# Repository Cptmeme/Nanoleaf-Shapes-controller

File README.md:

# Nanoleaf Shapes controller

An open-source replacement controller for **Nanoleaf Shapes** panels. A small interface board plugs into a
single panel edge and takes **42 V, GND and DATA** from it: no stock controller and no separate power supply.

<p align="center">
  
</p>
<p align="center"><em>An early board (foreground) driving nine Mini Triangles through a cut flex linker. Click for the video.</em></p>

It runs one of four firmwares:

- **WLED**, through a drop-in [usermod](wled/usermod/nanoleaf_shapes/) that needs no changes to WLED itself
  (recommended), or the original [core patch](wled/core-patch/). You get effects, 2D effects laid out on the
  real panel shape, the WLED apps and Home Assistant. See [`wled/`](wled/).
- **A standalone ESP-IDF firmware** with a Wi-Fi console, status page, OTA updates and a DDP receiver. It's
  useful for bring-up, protocol work, or as a network target for another WLED instance. See [`firmware/`](firmware/).
- **Matter over Thread**, built on [esp-matter](https://github.com/espressif/esp-matter): the panels become
  one Matter colour light for Apple Home, Google Home or Home Assistant, plus a switch that runs a moving
  rainbow. It talks Thread instead of Wi-Fi and pairs over Bluetooth. See [`matter-over-thread/`](matter-over-thread/).
- **[LeafBus](https://github.com/MyrikLD/LeafBus)**, MyrikLD's original MicroPython firmware, whose protocol work
  this project builds on. The panels become a DDP and E1.31/sACN pixel sink with a layout page. It needs three
  settings on this board, and hasn't been tested on it yet; see [Running LeafBus](#running-leafbus).

> **Status:** the hardware is built and working with an ESP32-C5 module, driving 9 Mini Triangles in chain,
> fork and ring layouts, with WLED (the core-patch build), with the ESP-IDF firmware, and as a Matter light in
> a Thread network.
> Hexagons and large Triangles are handled by the code but have not been tested on real panels yet.
> **Rev B is built and working**, with USB-C flashing, three buttons on the case and a printed
> enclosure. The project files in this repository are now **rev C**, which is rev B with the faults its
> bring-up exposed. No rev C board has been fabricated. See [Current board](#current-board-rev-c).

## Repository

| Path | Contents |
|---|---|
| [`hardware/`](hardware/) | Rev C KiCad project (schematic and PCB), fabrication files in `fab/`, and the printable case STLs in `mechanical/`. Rev B is built and working, rev C is rev B with its bring-up fixes and has not been fabricated |
| [`firmware/`](firmware/) | ESP-IDF firmware |
| [`wled/`](wled/) | WLED integration: the usermod (recommended) and the original core patch, each with build instructions |
| [`matter-over-thread/`](matter-over-thread/) | Matter-over-Thread firmware (esp-matter) |
| [`docs/protocol-notes.md`](docs/protocol-notes.md) | Panel bus behaviour measured on real panels, since merged into the LeafBus spec and credited there |

## Hardware

**Power:** 42 V from `J1` goes to a TPS54360 buck converter (`U1`), which makes 3.31 V (`R2` 47k / `R3` 15k,
`R5` 330k for 295 kHz, `L1` 33 µH, `D1` SS210). That's plenty for an ESP32 with Wi-Fi.

**Panel bus:** this uses the same method as the stock controller: two 74LVC1G125 tri-state buffers.
- `U4` transmits. Its output is enabled only while TX is active, by a one-shot (`D2` 1N4148W, `R7` 10k,
  `C17` 220 pF, about 1.3 µs), so the line is released between bytes.
- `U3` always receives, so the controller hears its own echo (the firmware strips it).
- `R1` (2.2 kΩ) sits in series with the bus and `R6` (1 kΩ) with RX. `R10` (1 kΩ) lets a GPIO drive the
  one-shot node for optional RS485-style direction control.

**Module:** any 16 × 24 mm module with the ESP-12F footprint. The footprint is drawn for the Wireless-Tag
WT0132C6-S5 (ESP32-C6); the working boards use a DOIT ESPC5-12 (ESP32-C5). The module sits on the back, and
is hand-soldered along with `SW1` and `SW2`.

### Module pins

| Net | Module pin (WT0132C6-S5 numbering) | ESP32-C6 | ESP32-C5 (ESPC5-12, verified) |
|---|---|---|---|
| Bus TX | 20 | GPIO3 | GPIO26 |
| Bus RX | 19 | GPIO10 | GPIO27 |
| One-shot (RC) node | 16 | GPIO7 | GPIO6 |
| BOOT button `SW2` | 18 | GPIO9 | GPIO28 |
| UART0 RX / TX | 21 / 22 | GPIO17 / GPIO16 | GPIO12 / GPIO11 |

For other modules, the ESP-IDF firmware finds the bus pins itself (`pinscan`) by exercising the on-board
`U4` → `U3` loopback.

### Connectors

| Connector | Pin 1 | Pin 2 | Pin 3 |
|---|---|---|---|
| `J1`, to a panel | 42 V | GND | DATA |

`J1` is three bare pads, not a header: the board clips beside a panel on a standard rigid Nanoleaf linker
and the linker's spring contacts press on them. There is nothing to wire up, and nothing to get the wrong
way round.

### Power and safety

- **Powered from the panels through `J1`:** the normal mode, and on a rev B board the only one. Wi-Fi,
  Bluetooth and Thread all work reliably on it.
- **Powered from USB:** rev C adds `D5`, a second SS210 from USB VBUS to the buck input, so the board runs
  from a USB host with no panel attached. With a panel connected, that node sits at 42 V and the diode is
  reverse biased, so nothing can reach the host. Without one, the buck runs from about 4.75 V, which leaves
  only ~0.25 V over the TPS54360's minimum: fine for bench flashing at 100-300 mA, not guaranteed on a long
  thin cable. On rev B, USB is data only and flashing needs a panel attached for power.
- **`D3`, an SMAJ48A, clamps the 42 V rail.** The board gets clipped onto live panels routinely, and
  hot-plugging into ceramic input capacitors can ring well above 42 V.
- **There is no fuse and no reverse-polarity protection**, left out on purpose: the linker mates one way
  only and `J1` is three bare pads, so there is nothing to connect backwards.

## Firmware

| | WLED ([`wled/`](wled/)) | Matter ([`matter-over-thread/`](matter-over-thread/)) | ESP-IDF firmware ([`firmware/`](firmware/)) |
|---|---|---|---|
| Use | Everyday lighting: effects, apps, Home Assistant | Smart-home light: Apple Home, Google Home, Home Assistant | Bring-up, diagnostics, protocol exploration |
| Network | Wi-Fi | Thread (needs a Thread border router); pairing over Bluetooth | Wi-Fi |
| Panel colours | WLED effects, including 2D on the real layout | One colour for all panels, white temperature, brightness; a rainbow switch | Console commands, or DDP from any sender |
| Touch | Not yet wired to WLED actions | Not yet exposed | Logged; "touch light" demo |
| Updates | WLED's update page | Serial (keeps the pairing); Matter OTA is enabled but untested | HTTP OTA with rollback |
| Chips | Usermod: builds for C5 and C6, not yet run on hardware. Core patch: tested on C5, C6 untested, also compiles for C3 and S3 | C5 (tested) and C6 (builds, untested) | Tested on C5 |

All three drive the panels the same way: they enumerate the layout at start-up, poll the panels every 50 ms,
and re-enumerate when panels are added or removed while running.

### Running LeafBus

[LeafBus](https://github.com/MyrikLD/LeafBus) is written for an original ESP32 wired to the panel through a
resistor. To run it on this board, change three things (this hasn't been tested on the board yet):

1. **MicroPython v1.29 or later for your module:** [ESP32_GENERIC_C5](https://micropython.org/download/ESP32_GENERIC_C5/)
   for the ESPC5-12, or [ESP32_GENERIC_C6](https://micropython.org/download/ESP32_GENERIC_C6/) for the
   WT0132C6-S5. See [Flashing](#flashing) for download mode.
2. **This board's bus pins in `config.json`:** `"uart": {"tx": 26, "rx": 27}` on the ESP32-C5, or
   `{"tx": 3, "rx": 10}` on the ESP32-C6.
3. **`open_drain=False` where `app.py` creates the bus:**
   `panelbus.PanelBus(tx=cfg['uart']['tx'], rx=cfg['uart']['rx'], open_drain=False)`. This board doesn't need
   open drain, because its tri-state buffer releases the line after every byte. LeafBus's open-drain switch
   also writes a register that only exists on the original ESP32.

Then copy the files as in LeafBus's quick start.

## Flashing

**Flashing goes over USB-C.** `U5`, a CH340C, carries UART0 with auto-reset, so there is no separate
adapter to wire up and no buttons to hold.

- **Rev C:** the standard tooling works as it comes. `idf.py -p PORT flash`, or `esptool` with its own
  default reset.
- **Rev B:** the CH340C's handshake lines reach the two reset transistors the opposite way round from the
  circuit esptool assumes, so its reset asserts BOOT where it means to assert EN and the chip never enters
  the ROM loader. It fails as `Invalid head of packet` or `No serial data received`, which reads like a bad
  cable. Use `firmware/tools/revb_reset.py download`, flash with `--before no_reset`, then
  `firmware/tools/revb_reset.py run`. Rev B's USB is data only, so the board needs a panel attached for
  power, and 115200 is more reliable than 460800 on this link.

After the first flash, WLED and the ESP-IDF firmware update over Wi-Fi. The Matter firmware updates over
serial again; without an erase, the pairing survives.

**Switching between firmwares:** each firmware has its own flash layout, so erase the chip when switching
(`esptool write_flash --erase-all`, or `idf.py erase-flash`). That also removes Wi-Fi settings and Matter
pairings.

## Protocol

The panel bus follows [LeafBus PROTOCOL.md](https://github.com/MyrikLD/LeafBus) (MIT): 1 Mbaud 8N1, single
wire, half duplex, with the controller initiating every exchange.

The measurements taken on this board were merged into that document in September 2026 and are credited
inline, so the specification and these panels now agree. The touch and status reply (`C0`) was the notable
exception and PROTOCOL.md describes it correctly as layout string order. The `0x20` status bit on the
power supply panel, the `10` marker on the first poll after a release and the panel centre lattice went in
with it.

The raw measurements stay in [`docs/protocol-notes.md`](docs/protocol-notes.md), together with the
recorded layout strings and a check of this project's layout parser against a hexagon capture.

## Current board (rev C)

> **Rev B is built and working. Rev C has not been fabricated.** Rev C is rev B with the faults that
> building and using a rev B board exposed, listed under *What rev B testing changed* in
> [`hardware/README.md`](hardware/README.md). The circuit is otherwise unchanged, so the description
> below covers both.

Rev B was a redesign rather than a revision. It clips beside a panel on a standard rigid Nanoleaf linker,
the same way the stock controller does, and sits in a printed case the same 1 cm thick as a panel.

### The board

A 106.35 x 21.70 mm trapezoid, two layers, 1.6 mm, 63 components.

| | |
|---|---|
| Panel connection | `J1`, three bare pads that the linker's spring contacts press on, carrying DATA, GND and 42 V. They sit in a pocket in the case, and the board has slots for the linker's snap hooks, as the panels' own PCBs do |
| Power | Still the panels' own 42 V, so there is no second supply. `U1` TPS54360 buck down to 3.3 V, with `D3` SMAJ48A clamping the 42 V rail |
| MCU | `U2` keeps the ESP-12F footprint, so an ESP32-C5 or ESP32-C6 module fits. An ESPC5-12 is what is actually fitted, because 5 GHz Wi-Fi and Thread both need the C5 |
| Panel bus | `U3` and `U4` 74LVC1G125 buffers driven by an RC one-shot, plus a 100 k pull-up that holds the bus high so the ESP32-C5's boot straps read correctly with no panel attached |
| Programming | `J3` USB-C and `U5` CH340C with auto-reset, so flashing needs no buttons and no separate serial adapter. Data only, the board still takes its power from the panels |
| Buttons | Three on the back for everyday use, pressed through the case. Reset and boot are there too and come off once the board is flashed |

### The case

An FDM printed tray, a lid and three separate button caps, generated from the board rather than drawn
against it: the real footprints, courtyards and heights are read out of KiCad and turned into geometry, so
the case cannot drift from the layout. [`hardware/mechanical/`](hardware/mechanical/) holds the STLs, ready
to print.

**10.00 mm thick**, 11.00 mm across a button cap, which matches a panel. Most of that is not free: the
linker fixes 6.55 mm of it before any design choice is made, since the plate recess and the plug depth
put the board surface 4.95 mm below the outer face.

The lid clicks into the tray on four beads, the outside corners and edges are rounded, and the three
button caps drop in from the inside and are held by a ridge. The board itself carries a keepout around
`J1` so components cannot creep into the space the linker pocket needs.

**The case has been printed and fitted to a real board**, which took several rounds. The button caps
held the switches closed until the third print, and the snap fit was settled by feel rather than by the
software clearance checks, which had already turned out to be wrong more than once here. The numbers in
`mechanical/` are the ones that worked on one FDM printer with my settings, so expect to tune
them for yours. See [`hardware/README.md`](hardware/README.md) for what specifically to watch.

<p align="center"><em>The board in its printed case, clipped to a panel edge and driving the run. The three caps are
the power, colour and brightness buttons.</em></p>

### Fabrication

`hardware/fab/pcbway/` holds the gerbers, drill files, BOM and centroid file, generated from the
current board. These are the rev C files. The rev B set, which is what was actually sent and built, is in the git history at the
commit before rev C replaced it. The rev B boards are sponsored by
**[PCBWay](https://www.pcbway.com/)**, who also supply the assembly.

Full design notes, including what was measured and what went wrong on the way, are in
[`hardware/README.md`](hardware/README.md).

## Thanks to PCBWay

The rev B boards and their assembly are sponsored by **[PCBWay](https://www.pcbway.com/)**, who got in
touch about LeafBus and were happy to back the hardware side of it too.

The whole thing went smoothly. What stood out most was the customer service. Replies came back fast,
sometimes within minutes, and the time difference worked for me rather than against me: a question sent
during my afternoon was usually answered by the time I got up the next morning. When I asked whether the
bare contact pads for the panel linker needed ENIG, I got a straight technical answer rather than a sales
one: ENIG if I wanted stable contact resistance and wear resistance, lead free HASL is fine if the usage
cycle is low and cost matters more. For a prototype with big spring contacts that was exactly the honest
answer, and it saved me the upgrade. They were equally helpful when I asked to cut the order back to
single sided assembly so I could solder the rest myself.

The files they were sent are the rev B set, which is in the git history at the commit before rev C
replaced it. [`hardware/fab/pcbway/`](hardware/fab/pcbway/) holds the current rev C files if you want to
order a board.

**The boards arrived and they work.** One was assembled with an ESPC5-12 and has been driving panels
ever since, through the panel bus, colour, touch and Matter over Thread. The single-sided assembly came
back correctly populated, and the bare linker contact pads came out clean.

## Credits

- [LeafBus](https://github.com/MyrikLD/LeafBus) by MyrikLD: the panel protocol specification, the geometry, and the
  original MicroPython firmware (MIT).
- **Christian Panton:** this board's PCB schematic is based on his write-up and schematics in
  [Nanoleaf Shapes deepdive, part 1](https://christian.panton.org/posts/nanoleaf-ctrl-pt1/), including the
  tri-state buffer interface the stock controller uses.
- [WLED](https://github.com/wled/WLED).
- [esp-matter](https://github.com/espressif/esp-matter) by Espressif (Apache-2.0), on top of the
  [Matter SDK](https://github.com/project-chip/connectedhomeip). The Matter firmware started from its light
  example (public domain / CC0).

## License

Hardware, the ESP-IDF firmware and the Matter firmware: [GPL-3.0](LICENSE). The files in [`wled/`](wled/)
build into WLED, which is licensed under EUPL-1.2, and are provided under WLED's licence.

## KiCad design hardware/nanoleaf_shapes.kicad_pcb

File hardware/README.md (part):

# Rev C

Rev C is rev B with the faults that rev B's own bring-up turned up. The board still clips beside a panel
on a standard rigid Nanoleaf linker, the way the stock controller does, and nothing about the shape of
the circuit has changed. It replaced rev B in this folder on 2026-11-10. Rev B is still in the git
history at the commit before that change.

The KiCad files keep the name `nanoleaf_shapes`: the schematic stores its component references under that
project name, and renaming it would make KiCad drop every reference.

> **The board and the case are generated, and the generators are not published.** Python writes the board
> outline, places the parts, cuts the linker footprint and builds the case; those scripts stay on the
> author's machine. Everything they produced is here in full: the KiCad schematic and board, the
> fabrication files, and the case as STLs you can print without running anything. What follows describes
> what the generators do and why, because that is what explains the board.

> ## Status
>
> **Rev B is built and working. Rev C has never been fabricated.**
>
> Rev B boards came back from PCBWay, one was assembled with an ESPC5-12, and the buck, the panel bus,
> enumeration, colour, touch, Matter over Thread, the three case buttons and the printed enclosure have
> all been exercised on real panels. Everything in this document that describes the circuit, the board
> and the case is backed by hardware.
>
> Rev C changes only what the next section lists. Those edits are checked but not built. ERC and DRC both
> pass with 0 errors and 0 unconnected items, and the fabrication files in `fab/` were regenerated from
> this board.
>
> The case has been printed and fitted repeatedly. The button caps took three rounds to stop them holding
> the switches closed, and the snap fit was settled by feel on real prints. Those numbers are measured
> rather than guessed now, but they are tuned for one FDM printer and will not transfer unchanged.

| | |
|---|---|
|  |  |

## What rev B testing changed

Rev B works. Building one and living with it still turned up a handful of things worth correcting before
another batch is made, and all of them are in rev C.

**Auto-reset was wired backwards.** The CH340C's DTR and RTS reached the wrong transistors, so esptool's
standard reset sequence drove EN and BOOT the wrong way round and the board would not enter download mode
on its own. Flashing a rev B board needs `firmware/tools/revb_reset.py`, which drives the two lines by
hand. Rev C swaps U5 pins 13 and 14, which puts Q1's emitter on DTR with its base on RTS and Q2's the
other way round, the usual DevKitC arrangement, so stock esptool works. `SW1` and `SW2` keep their
footprints even though they are not fitted, so the manual buttons can still be soldered on if auto-reset
misbehaves again.

**A via sat in the middle of the DATA linker pad.** Vias on this board are tented, but a pad carries its
own solder mask opening, so the hole stayed open exactly where the linker's spring contact lands. The
spring would have ridden over a plated crater, and an open hole there is somewhere for flux and debris to
sit. The via moved to just past the end of the pad, and the track now runs up into the pad on the front
copper instead.

**EN was not actually connected in the schematic.** The EN global label reached only one pin, so the
schematic disagreed with the board, which was routed correctly. ERC had been reporting it as an isolated
pin label the whole time.

**The schematic was missing part numbers.** Fourteen symbols carried no part number at all, which left the BOM
depending on the board alone and the two files disagreeing. Every part in the BOM now carries one.

**U2 named the wrong module.** The schematic still said WT0132C6-S5 while the board had been moved to the
ESPC5-12 that is actually fitted. Updating the PCB from the schematic would have pushed the wrong part
number back onto the board.

**The button nets were named after a guess.** They are now named for where the buttons sit on the case,
left and right, with only the power button keeping a function name, so the names stay true if the
firmware reassigns what the buttons do.

**R13's rotation disagreed with its own pad angles**, which made the board and its library copy differ
for no reason. Cosmetic, and fixed while the rest was open.

## Decisions

| | |
|---|---|
| Mounting | Beside a panel, joined with a standard **rigid** Nanoleaf linker, like the stock controller |
| Panel contact | Three exposed PCB pads that the linker's spring contacts press on, inside a printed pocket |
| Programming | **USB-C with a CH340C** USB-serial chip and auto-reset. Data only: the board runs from the panels |
| Enclosure | FDM-printed. The linker pocket is designed from a linker model plus caliper measurements |
| Module | ESP-12F footprint kept, so the ESP32-C5 and ESP32-C6 modules (and others) still fit |

## Proven blocks

Both of these are verified on real panels, so they carry over unchanged:

- **Buck converter** (TPS54360, 3.31 V): no brownouts at 42 V with Wi-Fi or Thread running.
- **Bus interface** (U3/U4 buffers, D2/R7/C17 one-shot, R1, R6): 1 Mbaud, touch and hot-plug all work.

## Circuit changes

**Added after the first schematic pass:**

- **D5**, a second SS210 (`C14996`), from USB VBUS to the buck input. The TPS54360 runs from 4.5-60 V, so the
  existing buck makes 3V3 from USB with no second regulator and no ORing logic: with a panel attached the node
  sits at 42 V and the diode is reverse-biased, so **nothing can reach the host**; with no panel it conducts and
  the buck runs from ~4.75 V. That leaves only ~0.25 V over the TPS54360's minimum, so a long thin cable under
  load could drop it out -- fine for bench flashing at 100-300 mA, not guaranteed. Before this, flashing needed
  a panel connected, because U5 runs off 3V3 and VBUS reached only U6.
- **C11** changed from a 22 uF electrolytic (`C47023097`) to a 2.2 uF 100 V X7R 1210 (`C5449052`, the same part
  as C1-C3). The 6.3 mm body stands 5.4-7.7 mm tall where the linker leaves 4.95. Four 2.2 uF in parallel give
  ~6 uF derated at 42 V against the TPS54360's 3 uF ceramic minimum. The electrolytic was also damping hot-plug
  ringing; that is acceptable here only because a rigid linker's lead inductance is tens of nH.

### Earlier changes

| # | Change | Why | Parts |
|---|---|---|---|
| 1 | **USB-C + CH340C with auto-reset** | The old serial header had no GND and no reset or boot control, and an adapter's 3.3 V cannot start the radios. Every serial flash needed BOOT + EN by hand, and several failed on loose wiring | USB-C receptacle (USB 2.0), CC1/CC2 5.1 kΩ to GND, CH340C (VCC = V3 = 3V3, 100 nF), 2 × NPN auto-reset (DTR/RTS → EN and the BOOT pad), ESD protection on D+/D− (USBLC6-2SC6) |
| 2 | **100 kΩ pull-up from COM to 3V3** | Without a panel, COM floats. On the ESP32-C5, bus RX is boot strap GPIO27, so download mode only worked with a panel attached. The first loopback frame without a panel also failed | 100 kΩ. U4 still pulls the far side down to about 0.07 V through R1 (2.2 kΩ) |
| 3 | **10 kΩ pull-up on module pad 11** | ESP32-C6 GPIO8 must be high for download mode, and the pad was left floating | 10 kΩ. On the C5 this pad is GPIO15, which is neither a boot pin nor used by the flash, so the pull-up is harmless there |
| 4 | **TVS on 42 V** | The controller will be clipped onto live panels routinely. Hot-plugging into ceramic input capacitors can ring well above 42 V; the TPS54360 is rated 60 V (65 V absolute maximum). Keep C11: its ESR damps the ringing | SMAJ48A (48 V standoff) |
| 5 | **Three contact pads instead of `J1`** | The pads replace the cut flex linker. **HASL is fine** -- an earlier note here called for ENIG, on reasoning that does not hold: HASL's ~10-25 um crown on a 1.50 mm pad is nothing against a spring finger's compliance, and the linker inserts, so the springs wipe the pads as they seat rather than pressing statically on tin oxide. ENIG's immersion gold is only ~0.05-0.1 um and wears through in a few dozen matings anyway; the finish for a mated contact is hard electroplated gold, which is a different and dearer process. If a board ever misbehaves, a burnish or a dab of contact enhancer costs a few euros. | Pads per [Mechanical](#mechanical) |
| 6 | **D1 next to U1** | It sat 16 mm away, which enlarges the switching loop | Layout only |
| 7 | Status LED on module pad 18 | Shows pairing or Wi-Fi state. Optional | LED + resistor. Pad 18 is C5 GPIO8 / C6 GPIO19; neither is a boot pin |
| 8 | Test pads for COM, 3V3, GND, TX0, RX0 | Probing and a fallback serial connection | Pads only |

**Dropped:** reverse-polarity protection. The Nanoleaf connector only fits one way.

## Schematic

`nanoleaf_shapes.kicad_sch` has all the changes above. The original circuit is untouched, so the new parts sit in
their own block on the right of the sheet (now A3). Like the rest of the schematic, they connect through global labels.

| Refs | Part | Nets |
|---|---|---|
| J3 | USB-C receptacle (HRO TYPE-C-31-M-12 footprint) | `USB_DP`, `USB_DN`, `USB_CC1`, `USB_CC2`, `USB_VBUS`, `GND`; SBU not connected |
| R11, R12 | 5.1 kΩ | CC1, CC2 to GND (USB device) |
| U6 | USBLC6-2SC6 | ESD protection on D+/D−, referenced to `USB_VBUS` |
| U5, C22 | CH340C, 100 nF | VCC and V3 on `3V3`; TXD → `RX0`, RXD ← `TX0`; ~DTR → `DTR`, ~RTS → `RTS` |
| Q1, Q2, R13, R14 | MMBT3904, 10 kΩ | Auto-reset as on Espressif's DevKitC: Q1 pulls `BOOT` (pad 12) low, Q2 pulls `EN` low |
| R15 | 100 kΩ | `COM` to `3V3` |
| R16 | 10 kΩ | `PAD11` to `3V3` |
| D3 | SMAJ48A | `42V` to `GND`, cathode on `42V` |
| R17, D4 | 1 kΩ, 0603 LED | `LED` (pad 18) through the resistor to the LED, to `GND` |
| TP1, TP2 | Test pads | `GND`, `COM` |
| J1 | Linker pads | Footprint `nanoleaf:Nanoleaf_Linker_Pads`; 1 = 42 V, 2 = GND, 3 = COM, as before |
| J2 | Test pads | Footprint `nanoleaf:TestPads_1x03_P2.54mm`: RX0, TX0, 3V3 (with TP1 for GND) |

In the existing circuit: `EN` and `BOOT` labels on U2's pins (SW2 moved to the right to make room, same
connection), and pads 11 and 18 lost their no-connect flags.

**Checked with kicad-cli 10.0.3:** ERC gives **0 errors and 41 warnings**, every one of them "Unspecified and
Passive pins connected", because the easyeda2kicad symbols give their pins no electrical type. `U2` alone
accounts for 15, `U1` 9, `U4` 7 and `U3` 6, across 32 symbols in total: a symbol library artefact, not a
circuit problem. The board before this one reported the same 41, plus an `isolated_pin_label` and a stray
no-connect flag that sat in empty space on the sheet. Both are now gone. A netlist comparison against that
board shows every new net with exactly the intended pins, and every connection it already had still intact.

**Part numbers:** the `LCSC` fields carried copy-paste errors: J1 and U4 had C1525 (the 100 nF capacitor),
J2 C52923, SW1 C5449052 and SW2 C4211. They didn't matter, because the BOM listed U3/U4 correctly and left the
others out. Rev B fixes them: U1 C44377, U3/U4 C52140413, and no number for J1, J2, SW1 and SW2 (not
assembled). J1 and J2 are now marked "not in BOM". The new parts reuse the
design's numbers where the value already exists (10 kΩ C25744, 1 kΩ C11702, 100 nF C1525). The rest still need
picking; commonly used ones to check stock against are CH340C C84681, USBLC6-2SC6 C7519, MMBT3904 C20526,
HRO TYPE-C-31-M-12 C165948, 5.1 kΩ 0402 C25905 and 100 kΩ 0402 C25741, plus an SMAJ48A and a 0603 LED.

**USB ground:** with USB connected, the computer's ground joins the panels' ground. That's fine as long as the
Nanoleaf power supply's output is isolated, which is normal for a wall adapter; check it on the supply's label.

## Module pads

The KiCad footprint numbers the pads differently from the module datasheets. Footprint pads 1–8 are datasheet
pins 1–8, pads 9–16 are pins 15–22, and pads 17–22 are pins 9–14 (the short end). Checked against the pad
positions in the PCB and the pins verified on the ESP32-C5 board. Boot pins from ESP-IDF's GPIO tables:
C5 GPIO2, 7, 25, 27, 28; C6 GPIO4, 5, 8, 9, 15.

| Footprint pad | Datasheet pin | ESPC5-12 (ESP32-C5) | WT0132C6-S5 (ESP32-C6) | Rev B use |
|---|---|---|---|---|
| 3 | 3 | EN | EN | EN, auto-reset |
| 8 | 8 | 3V3 | 3V3 | |
| 9 | 15 | GND | GND | |
| 10 | 16 | GPIO6 | GPIO7 | One-shot node (R10) |
| 11 | 17 | GPIO15 | GPIO8 (boot pin) | 10 kΩ pull-up |
| 12 | 18 | GPIO28 (boot pin) | GPIO9 (boot pin) | BOOT button, auto-reset |
| 13 | 19 | GPIO27 (boot pin) | GPIO10 | Bus RX |
| 14 | 20 | GPIO26 | GPIO3 | Bus TX |
| 15 | 21 | GPIO12 (U0RXD) | GPIO17 (U0RXD) | CH340C TXD |
| 16 | 22 | GPIO11 (U0TXD) | GPIO16 (U0TXD) | CH340C RXD |
| 17 | 9 | GPIO7 (boot pin) | GPIO18 | Free: avoid |
| 18 | 10 | GPIO8 | GPIO19 | Status LED |
| 19–20 | 11–12 | GPIO9, GPIO10 | GPIO20, GPIO21 | Free |
| 21–22 | 13–14 | GPIO13, GPIO14 (native USB) | GPIO22, GPIO23 | Free |

The ESP32-C5 module brings out native USB on pads 21–22, the C6 module doesn't. The CH340C works with both.

## Board

An **upside-down isosceles trapezoid**: the long parallel side is the joint edge, against the panel, and the
legs taper away from it at 60 deg. That is not a styling choice -- a hexagon's corner is 120 deg, so each leg
is the panel's own adjacent edge continued straight through its vertex. Carried to its end the two legs would
close into an equilateral triangle; this is that triangle cut off at `CASE_DEPTH`, which is the one dimension
free to grow for the electronics.

| | |
|---|---|
| Case | 113.00 mm on the joint edge, tapering to 74.89, 33.00 mm deep. The 113 sits just inside a hexagon's 114 mm edge, so the case never overhangs the panel it joins |
| Board | 106.30 -> 72.70 mm, 29.10 mm deep, 2605 mm2 |
| Joint edge | the **case** edge, not the board edge, is the datum for every linker dimension. The plate straddles it, 20.02 mm onto the panel and 20.02 onto the case, so this line has to fall halfway along the linker or it will not reach the panel. The board sits `JOINT_INSET` = 2.00 mm inside it, leaving a wall |
| Thickness | ~11 mm, against a panel's 6 mm (10 mm mounted). Forced, not chosen: the linker eats 4.95 mm from the back face down to the PCB surface before the 1.60 mm board. The controller stands proud |

### Placement

The earlier layout was discarded rather than extended, because its decoupling was in the wrong place -- all six
100 nF caps sat 8-14 mm from the module's 3V3 pin, in a tidy row, where trace inductance makes them useless,
and the buck's catch diode was 17.9 mm from U1 with two of three input caps 12-15 mm from VIN.

| | before | now |
|---|---|---|
| Module 3V3 to nearest 100 nF | 8.17 mm | **1.93 mm** (C5, C4, C6 within 3.7) |
| U1 VIN to nearest input cap | 4.36 mm | **2.51 mm** |
| U1 SW to the catch diode | n/a | **3.03 mm** |
| D1 ground to U1 ground | 17.89 mm | **9.80 mm** |

**Everything is on the front.** The module and both buttons used to be on the back, which makes the board
double-sided to assemble; with all 60 parts on F.Cu, an assembler can build the whole thing, so a populated board is
an option rather than a hand-soldering job. The cost is that the buttons face the wall, which is tolerable --
they are flashing aids, and `download` replaces them anyway.

Flipping the module to the front **mirrors it**, so it is placed at **rot 180**: at rot 0 the antenna would
point into the middle of the board and all seven signal pads would face the 3 mm strip under the joint edge.
At 180 the antenna overhangs towards the right leg and the signals fan down into open board.

| Area | Holds |
|---|---|
| top right | the module, in the corner, with its antenna pointing out along the top edge and the board past it cleared of copper on both layers |
| above it | the 3V3 decoupling row and the enable network, sitting on the module's own pins |
| top left | the buck, shifted right to clear J3. The hot loop survived the shift: VIN to the nearest input cap 2.51 mm, SW to the catch diode 2.53 mm |
| centre | the bus buffers, with COM dropping straight into them from the linker above |
| left leg | **USB**. J3 rotated 300 deg so its mouth faces out of the 60 degree bevel, with U6's ESD clamp in the nearest free slot above it |
| bottom right | auto-reset, buttons, status LED and the serial pads, under the module they talk to |

**Why the USB is on the leg, and what it cost.** Putting it there frees the whole bottom edge for the five
buttons. Every usable 16-pin USB-C footprint has four to six through-holes -- the only hole-free one in KiCad
is a 6-pin power-only part -- and on the bottom edge those holes sat under the button row. On the leg they land
at y 52.6..62.2, well clear of it.

The cost was repacking the buck: J3's rotated body reaches x 52.63, so D1, L1 and U1 all shifted right. The hot
loop came through unchanged, but three things got worse:

- **U6, the ESD clamp, is 7.8 mm from J3's D+/D- pads** instead of ~2.4 mm. J3's own courtyard occupies
  everything beside its pads, so the nearest free slot is above it. It is still first in the signal path, ahead
  of the CH340C, which is what matters most -- but closer would be better.
- the compensation passives (C12, C13, R4) were displaced to wherever fits around the shifted buck;
- the CC resistors sit 6 to 12 mm from their pads, which is cosmetic since they are DC pulldowns.

**The module's printed antenna is a keepout**, x 118.0..126.4, y 48.8..67.0 (the `ANTENNA` keepout). It
overhangs the module's pads by 8.62 mm. Nothing is placed in it and the ground pour has a hole punched in its
polygon there -- a rule area would be the obvious way, but KiCad 10's `ZONE_FILLER` ignores those when driven
from Python.

**The corner past the antenna is cleared too.** That keepout only covers the antenna's own rectangle, and
when the outline was widened to 106.3 mm the board grew out past it with the pour following -- 163 mm2 of
board beyond x 126.4, 86% of it ground on both layers, reaching 13.6 mm into the direction the antenna
radiates. A printed antenna needs the copper cleared where it radiates, not just underneath itself. That
copper has since been removed: **0 mm2 on both layers** beyond x 126.4, and no via is placed past x 121.2.

### Why the board is this size

Width is not free: it is set by the hexagon's 114 mm edge, which the case has to sit inside. **Depth is the
only free dimension**, so it is what sets the area. The first packed layout was 43.08 mm deep and only 37% of
its front was covered in parts; at 33.00 it is **2605 mm2 against 3279, a 21% saving**, with the front about
half covered -- dense for two layers but still hand-routable.

What stops it going further: the module is 17.85 mm tall and J3 is 9.47 mm deep and has to reach the far edge,
so 27 mm is about the floor, and at that depth the bottom band gets too tight for J3 plus the bus interface.

`J2`, the old RX0/TX0/3V3 header, is **gone**. The CH340C gives the same UART0 over USB with auto-reset on top,
and TP1/TP2 already cover scoping the bus, so it was dead weight. If the USB path ever needs bypassing, those
signals are still reachable at U5's pins.

### User buttons

Five switches on the **back**, the room-facing side, so they can actually be pressed: **three user buttons**
-- power and the two that step the colour cycle -- plus reset and boot, moved across from the front, which
had no room left for them and where they would have faced the wall anyway. They were laid out for power,
brightness up and effect, which is where the original net names came from.

They sit on the **board midline, y 56.825**, and are centred on the two areas the linker cut-out leaves. The
cut-out spans x 79.61..94.06, and at the midline the board runs x 39.93..133.74, so the areas either side of
it are **39.676 mm wide each** -- symmetric by construction:

Board x runs the opposite way from what somebody at the wall sees: the switches are on the back and the
case shows that face to the room, so the **highest x is the leftmost button**.

| | x | Where on the board | Seen from the room |
|---|---|---|---|
| SW6 `BTN_PWR` | 113.90 | right area, **midpoint** | leftmost, the large cap |
| SW4 `BTN_LEFT` | 69.69 | left area, three-quarter point | middle |
| SW3 `BTN_RIGHT` | 49.85 | left area, quarter point | rightmost |

**Renamed on 2026-11-10.** They were `BTN_PWR`, `BTN_UP` and `BTN_FX`/`BTN_DN`, from an earlier plan of
power, brightness up and effect -- and by then `BTN_PWR` sat on the button furthest from the power
function. Reading those names off the schematic is what put power on the wrong switch in the Matter
firmware first time round.

Only the power button carries a function name now, because it will always be the power button. The other
two are named for **where they are**, left and right of each other as somebody at the wall sees them, so
the schematic cannot go stale again when the firmware reassigns what they do. At the moment they step the
colour cycle, `BTN_LEFT` back and `BTN_RIGHT` forward.

The left pair splits its area into four equal parts. SW6 is at its area's midpoint rather than a quarter
point because the brightness-down button that shared that side was removed -- it sat over the module's
printed antenna -- and FX moved to the middle of where the two had been.

Read from the back, the side being pressed, the mirroring puts them in the order **effect, brightness +,
power** from left to right.

The user buttons are **C&K PTS645**, 6 x 6 mm with four gull-wing pads -- far easier to hand-solder than the
two-pad parts, and a real MPN rather than a house number.

**On switch size.** A swap to a generic 6x6x5 SMD part was looked at and dropped: the PTS645 *is* a 6 x 6 mm
part, so the land pattern would not shrink. Its 10.19 x 6.89 mm courtyard is simply what a 6 x 6 body with
gull-wing leads needs, and Omron's B3S-1000 lands within 0.01 mm of it. The saving only arrives with a
smaller body -- Alps SKQG or XKB TS-1187A, both 5.2 mm square, come in at 8.50 x 5.50 and 7.50 x 5.60 mm,
about **40% less area, 85 mm2 across the three** -- and TS-1187A goes to 5.0 mm height, so the tall button
survives. Not done: the board is routed and DRC-clean, and 15 track ends land on these pads.

**Reset and boot are not needed in normal use.** The auto-reset circuit drives EN and BOOT from DTR/RTS, so
esptool handles both without anyone touching a button, and the firmware's `download` command covers it too.
They are kept for rev B purely as bring-up insurance: that circuit is new here and has never been tested, and
with J2 gone there is no other serial path if it misbehaves. Not the only fallback -- Q1's collector and an
EN-side pad can be shorted to TP1 with tweezers -- but a button beats tweezers on a first spin.

They cost no board area, since the back is otherwise empty, and they use the smaller 4-pad **C&K KMR2**
(5.69 x 3.69 mm courtyard against the PTS645's 10.19 x 6.89). Both sit just right of the linker cut-out at
x ~101.5, under the module they talk to: SW2's nearest pad is **1.67 mm** from the module's edge pads.
**Drop them in the next spin once auto-reset is proven**, or mark them DNP now: the pads cost nothing and can
be populated if the first boards misbehave.

### U1's thermal vias

The TPS54360 sheds its heat through its exposed pad, so that pad needs a path to the ground pour on the
back. The easyeda2kicad footprint provided one: four plated holes inside the pad. Right idea, wrong place
to put it.

Expressing them as footprint pads cost more than it bought. They carry **no pad number**, so no schematic
pin can match them -- four `net_conflict` parity warnings, and their GND net had to be set on the board by
hand rather than coming from the netlist, where an Update PCB from Schematic could quietly drop it again.
And a plated hole inside an SMD part's courtyard is exactly what `pth_inside_courtyard` looks for: two more
errors, against SW4 on the other side. The same library also gave them `*.Cu *.Paste *.Mask`, so they had
mask openings and paste apertures on *both* faces, leaving bare GND copper 0.271 mm from SW4's BTN_LEFT pad.

They are now **ordinary GND vias on the board**, placed by hand, and gone from both the board footprint and
the library copy. Nothing is lost: same four holes, same 0.61 / 0.30 mm, same
net, same places, still inside the exposed pad's mask and paste window, and tented on the back by default.
Four warnings and two errors stop being asked about, and U1 matches its library again.

| via | x | y |
|---|---|---|
| | 71.32 | 53.35 |
| | 72.32 | 53.35 |
| | 71.32 | 54.35 |
| | 72.32 | 54.35 |

**What it costs: vias do not move with U1.** That is precisely why the footprint author put them in the
footprint, and why KiCad's own `SOIC-8-1EP_..._ThermalVias` does the same. Fine while U1 is placed and
routed -- but if it ever moves, the vias stay behind and nothing warns you.

The exposed pad's own paste aperture is still a solid 2.00 x 2.00 mm, 100% coverage, where KiCad's
equivalent splits it four ways at 65% and IPC-7093 wants roughly 50-80%. Unchanged and still open.

### Ordering

PCBWay sources globally by manufacturer part number through authorised distributors, with kitted,
partial-turnkey and full-turnkey options. The BOM it needs is designator, quantity, package and
*manufacturer part number*; for passives with no MPN, value and package are enough. It also wants a
centroid file whose designators match the BOM, and an assembly drawing or silkscreen showing polarity.
All of that is in `fab/pcbway/`.

- **Spell out what must not be substituted.** The 100 V X7R ceramics on the 42 V rail are the dangerous
  ones: a substitution to a lower voltage or a Y5V dielectric breaks the design silently.
- The `LCSC` `C...` numbers in the schematic identify the exact part at a distributor. Take the
  manufacturer part number from there: <https://www.lcsc.com>, <https://www.digikey.com>,
  <https://www.mouser.com>.

### Ground stitching

**197 vias on the board, 168 of them GND.** 43 came from the stitching grid, 0.6/0.3 mm, on a
**3.0 mm grid centred on the board**, so they fall in seven straight rows at
y 47.825 to 65.825 and in straight columns. The grid is generated and then every point that would not make
a good via is thrown away. Of the 219 grid points that land on the board:

| Rejected for | Count |
|---|---|
| the pour only reaches one layer there, so the via would stitch nothing | 108 |
| the antenna keepout and the board beyond it | 27 |
| too close to a pad | 26 |
| the linker slots | 8 |
| the board edge | 6 |
| a non-GND track | 1 |
| **kept** | **43** |

The pour test is the one that matters: a candidate only survives if its whole 0.6 mm pad -- centre plus four
edge probes -- sits inside the GND fill on **both** F.Cu and B.Cu. That is why the row at y 62.825 has only
two vias: the button row blocks the back pour across the middle of the bottom edge.

Clearance to other copper is checked at **0.30 mm**, three times the 0.1 mm netclass rule, so the grid keeps
its margin even where the routing is tight. The script asserts that the track, footprint and zone counts are
unchanged, and takes a timestamped backup, so it cannot disturb hand routing.

#### Stitching the re-routed board: 1.4 mm grid, 256 GND vias

The re-routed board carries the real stitching. It was built in `replan/` and **promoted to
`nanoleaf_shapes.kicad_pcb` on 2026-10-10** once DRC came back clean, so `replan/` is now a
superseded copy, since deleted. The board and schematic in `hardware/` are the live ones. Pitch went from 3.0 mm to **1.4 mm** after a
sweep (3.0 -> 42 vias, 2.5 -> 48, 2.2 -> 72, 2.0 -> 79, 1.8 -> 96, 1.6 -> 121, 1.4 -> 177), giving **15 rows**
and **256 GND vias** on the board as shipped: the grid contributed 177, the island fix added the two
that rescue stranded ground pins, one was dropped as too close to Q2, and the rest were placed by hand. Of 1005 grid points on the board:

| Rejected for | Count |
|---|---|
| the pour only reaches one layer there | 495 |
| the antenna keepout and the board beyond it | 124 |
| too close to a pad | 93 |
| the board edge | 66 |
| a non-GND track | 32 |
| the linker slots | 16 |
| hole to hole | 2 |
| **kept** | **177** |

The result is **one** connected body of ground copper, 2221 mm² over 16 islands on both layers, and DRC
reports **0 errors and 0 unconnected items**. What is left over is four fill artifacts at the zone boundary --
a 0.142 mm² hairline 0.01 mm wide and three zero-area specks -- all an order of magnitude below the 0.1 mm
minimum feature any fab can etch, so no copper will actually exist there.

#### Two ground pins the grid could not reach

A grid alone was not enough. Two F.Cu pours stayed electrically separate, and each held a **ground pin**:

| Island | Area | Stranded pin |
|---|---|---|
| x 54.35..58.00, y 51.42..56.85 | 4.03 mm² | `U6.2`, GND of the USBLC6-2SC6 USB ESD array |
| x 99.61..101.24, y 59.81..62.14 | 2.07 mm² | `U3.3`, GND of the 74LVC1G125 data buffer |

`U3.3` is the buffer's own ground, so the part would not have worked. Neither island took a grid via: island A's
grid points all fell inside SW3's pad keepout, and island B is boxed in so tightly by R1 and U4 that a
breadth-first path search found **no escape on F.Cu at all** -- not a 0.25 mm track, not even 0.12 mm at 0.15 mm
clearance. A via was the only way out of island B.

One standard 0.6/0.3 mm via goes at the widest point *inside each island*,
found by binary-searching the largest free disc with KiCad's own collision test. Two details matter:

* The search has to be constrained to the island polygon, not the pour at large. The widest point *near*
  island A is in the main pour a fraction of a millimetre outside it, and a via there stitches nothing.
* A `pad_standoff` keeps the via off pad copper so reflow cannot wick solder down the barrel. At 0.20 mm the
  via lands 0.89 mm from `U6.2` with 0.352 mm of clearance -- close enough to keep the ESD return path short.
  Raising it to 0.40 mm buys nothing and forces the via into a 0.203 mm gap instead.

Island B's via clears `R1.1` by **0.205 mm** against the board's 0.200 mm minimum. It passes, but it is the
tightest copper on the board; nudging R1 a tenth of a millimetre would make it comfortable.

#### Why a hand-written clearance test is not good enough

The 1.4 mm grid dropped one via 0.131 mm from `Q2` pad 3, under the 0.200 mm minimum. The test compared
against `GetSize()`, which is in the pad's **own frame**: Q2 sits at 90 deg, so its 1.475 x 0.600 mm pad read
as 0.600 x 1.475 and the via cleared on the y axis by arithmetic that described a pad in the wrong
orientation. The same code also filtered tracks on `GetClass() == "PCB_TRACK"`, which skips `PCB_ARC`
entirely, and approximated every pad as a rectangle.

The check now asks KiCad instead -- `GetEffectiveShape(layer).Collide(disc, clearance)` -- which is
exact and covers rotation, roundrects, ovals, custom pad shapes and arcs for free. An audit of all 229 vias
with the exact test found exactly one violation, the Q2 one, and it is gone. The 24 vias sitting between
0.20 and 0.30 mm are all hand-placed and legal.

### State

DRC: **0 errors, 0 unconnected items, 0 schematic-parity issues.** 14 violations, all warnings, all
cosmetic:

| | |
|---|---|
| 9 silkscreen | 7 `silk_overlap`, 2 `silk_edge_clearance`. PCBWay clips silk off pads anyway. |
| 3x `text_height` | J1's DATA/GND/42V labels at 0.6 mm against a 0.8 mm rule. Deliberate -- they have to fit on the tongue. |
| 2x `lib_footprint_mismatch` | J3 and U5, both **1 nm rounding noise**: a few line endpoints stored as `4.699999` where the library has `4.7`. Pads, layers, shapes and polygons are identical. |

The errors that used to sit here are gone for three different reasons, worth keeping apart: the two
`pth_inside_courtyard` and the four `net_conflict` went when U1's thermal vias stopped being footprint
pads; the two `clearance` against the GND zone were a **stale pour** after a hand edit, cleared by a
refill, not by any geometry change; and U1 no longer differs from its library because the library was
corrected alongside it.

**Board and schematic agree exactly**: 63 symbol instances, 63 footprints, identical reference lists, and
every footprint has all of its pads inside the outline. Nothing is parked off-board.

**42 V creepage** was re-checked after the netclass clearance was dropped to 0.1 mm: the tightest same-layer
gap on the 42 V net is **0.200 mm**, to C1 pad 2 on F.Cu. IPC-2221 wants 0.13 mm for 31-50 V under solder
mask, so the lowered clearance has not compromised it.

## Mechanical

From Christian Panton's [write-up](https://christian.panton.org/posts/nanoleaf-ctrl-pt1/): the linker tabs carry
the spring contacts, and the devices (panels, power supply, controller) only have exposed PCB pads, held in place
by the moulded case. His pads measure **about 10 × 1.5 mm with 1 mm gaps**. The pad order is 42 V, GND, DATA,
with GND in the middle.

### Linker geometry

From [Nanoleaf Panel Connector](https://www.printables.com/model/997500-nanoleaf-panel-connector) by thegestalt,
a printable contactless linker that clips into the panels. It is licensed CC BY-NC, so it's used here only as a
dimensional reference: neither the STL nor a remix of it goes into this GPL-3.0 repository, and the pocket is
modelled from the numbers below.

| Feature | Size |
|---|---|
| Base plate | 17.3 × 40.0 mm, 2.37 mm thick, 2.0 mm corner radius. It sits in a recess in each panel's back, flush |
| Plug, one per end | 11.4 mm wide × 12.5 mm long, 2.5 mm tall; the outer end is chamfered |
| Gap between the two plugs | 9.0 mm, so a pocket starts about 4.5 mm in from its panel's edge |
| Plug corners | 3.0 mm radius |
| Snap hooks | Two per plug, one on each side, 2.7 mm wide, centred along the plug (4.9–7.6 mm from either end) |
| Locating posts | Plain, non-grabbing posts beside the hooks, found on a real linker by the test print below. They need the PCB slot to run the plug's whole length, not just the hook band |
| Hook barbs | Stick out 0.41 mm past the plug sides, widest 3.08 mm below the plate's inner face, which is 0.6 mm *below* the plug top; hook tips reach 3.63 mm below it |

### Pads and pocket

- **Plate recess:** the panels have a recess for the linker plate, so a fitted linker is flush with the back. The
  enclosure gets the same recess, 2.37 mm deep.
- **Pad depth:** the plug's flat top lands (almost) on the pads, and the linker's springs press on them from
  there. So the PCB surface sits 2.48 mm below the recess floor, plus a 0.1 mm gap: 4.95 mm below the
  enclosure's back.
- **Pad order**, measured on a panel: seen from the back of a panel with its edge at the bottom, 42 V is the left
  pad. The linker crosses the outer contacts over, so the controller follows the same rule as a panel. **Seen
  from the pad side with the joint at the top, the pads are DATA, GND, 42 V from left to right.**
- **Slots beside the pads:** the hooks reach deeper than the pads, so the PCB is cut away beside each one and the
  barbs snap under the pocket wall into the gap. A real linker also has plain locating posts, so the cut runs the
  **whole length of the plug** rather than only the hook band: 3.30 × 13.10 mm each side. The panels' own PCBs have
  the same full-length slots, and theirs are wider still. The outer edge is deliberately far outboard of the
  modelled barb (`SLOT_OUT` 1.20 mm, not `BARB_OUT` 0.41): the slot must never be what stops the barb springing,
  and the width costs nothing out there. **It does not set how hard the linker grips** — that is
  `BARB_OUT - CLEAR`, the barb's reach past the pocket wall's inner face, and the slot plays no part in it.
- **Pad position along the linker:** the springs sit in the middle of the plug (checked on a real linker), so the
  pads are centred on it, 10.77 mm from the joint.

The three pads ship as a KiCad footprint, `nanoleaf.pretty/Nanoleaf_Linker_Pads.kicad_mod`: bare copper with
no paste, the snap-hook slots on Edge.Cuts, and a courtyard covering the printed pocket walls so nothing else
is placed where the case needs the room. The project's `fp-lib-table` names that library `nanoleaf`.

Checked in software with the linker model sitting flush in the recess: the plate and plug touch nothing,
and the barbs catch under the pocket wall after 0.3 mm of pull.

### Test print

The test piece prints as a **split pair**, both halves as they come, bottom on the bed, stacked on two 3 mm
registration pins. Neither half has an overhang. There is a one-piece version as well, for reference and for
a resin or machined part. On FDM that one prints the ledge the barb catches as a cantilever reaching inward
over the slot, so the latching corner is the droopiest point of an overhang and rounds away. Then push one end of a real rigid linker in:

1. It clicks in and holds.
2. The linker plate sits flush in the recess, level with the top face.
3. The springs touch the floor: look for marks, or feel them compress.

If the fit is tight or loose, or it seats without latching, change the clearance. It is the only lever on
grip: tighter clearance, deeper grip, until the plug stops going in.

**Result, 2026-10-03:** the first print was cut only to the hook band (`HOOK_Y`), and the linker's plain locating
posts fouled the floor. The slots now span the plug (`SLOT_Y`), which both the test piece and the footprint
follow. Still to measure on a panel PCB: how much wider than the hooks the real slots are.

**Result, 2026-10-04:** the linker seats fully and flush but does not latch. Two causes, both addressed, neither
confirmed yet, as there are no calipers to hand:

- the ledge was an unsupported inward cantilever, hence the split print above;
- at `BARB_OUT` 0.41 and `CLEAR` 0.20 the grip was only **0.21 mm** nominal, which FDM tolerance alone can
  swallow. `BARB_OUT` came from the community model, which was already wrong about the locating posts, so it may
  simply be larger in reality; the slot was widened outboard so that a larger barb is free to deploy.

Next print: the split pair at the default clearance, then `0.10` if it still will not catch. If the tighter one
latches, the barb is real and the grip was the problem; if neither does, measure a real barb before changing
anything else.

### Enclosure

Two printed parts: a **tray** the board drops into, and a **lid** carrying the three back buttons.
Both are generated, along with a printable stand-in for the assembled board, from `parts.json`, which is
written straight out of the board under KiCad's own Python. So the case is cut to the board KiCad actually
has, not to a drawing of it.

**Nothing in the thickness direction is a free choice until the board's back face.** The linker fixes the
first three rows: the case edge has to fall halfway along the linker, and the test print proved the
recess and pocket against a real one.

| z | | |
|---|---|---|
| 0.00 | outer face, **wall-facing** | the linker plate recesses into this |
| 2.37 | plate recess floor | `PLATE_T` |
| 1.10 | component cavity ceiling | 3.85 mm clear, for J3's 3.50 |
| 4.95 | board, front surface | `+ PLUG_H 2.48 + TOP_GAP 0.10` |
| 6.55 | board, back surface | `+ BOARD_T 1.60` |
| 8.05 | top of the back parts | `+ 1.50`, the user buttons |
| 8.40 | lid inner face, the seam | `+ BACK_GAP 0.35` |
| 10.00 | outer face, **room-facing** | `+ LID_T 1.60` |

**Total 10.00 mm**, and 11.00 mm across a button pad -- the same 1 cm as a panel. The board's front faces the wall, because that is
the side the linker pads are on, which is what puts the buttons on the room side where they can be pressed.

**One open cavity, not a pocket per part.** The front of the board sits in open air. Giving each part its
own pocket was tried and dropped: it makes a stiffer tray, but it wraps every part in plastic 0.25 mm away,
and the buck has to shed its heat somewhere. **80% of the board's area is open to the cavity** at the board
plane.

What that costs is support, which comes back three ways. A **1.20 mm rim** round the edge, opened up
wherever a front part reaches into it. The **plate region**, solid under the recess except where a part
needs the room. And **eight 1.80 mm posts**, 3.85 mm tall, out where the rim cannot reach -- chosen, not
placed: parts, pocket and recess are subtracted from the interior, what is left is eroded by the post's own
radius to give where a centre may sit, and candidates are picked greedily furthest-from-the-rest so they
spread. They are small because the gaps between parts are a thin web rather than open blobs; at 3.00 mm
only three places took one, at 1.80 mm eight do, from x 37.8 to x 135.8.

**The linker pocket does not need the cavity filled to stop being an island -- it needs attaching.** That
is the recess wall ring's second job: running it from the outer face up to `Z_CAV_PLATE` rather than
stopping at the recess floor, it overlaps the 1.10 mm floor below it and the recess floor beside it, so the
whole plate region, pocket included, hangs off the tray proper instead of off its root at the joint edge.

**Reliefs are measured against the recess as cut.** The recess is the plate plus 0.20 mm of fitting
clearance, and for a while the relief check used the bare plate instead. That leaves a 0.20 mm band where a
part gets no relief and the shallow rule still applies -- a clash rather than a hole, which is worse. Both
now use the same outline. A part needing the floor cut back is only a problem when the floor goes under
0.60 mm: C14 and C15 take theirs to 0.78 mm, which is still a floor, and only D3 breaks through.

**The wall around the recess is carried up to the board, not just to the recess floor.** Section the case
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
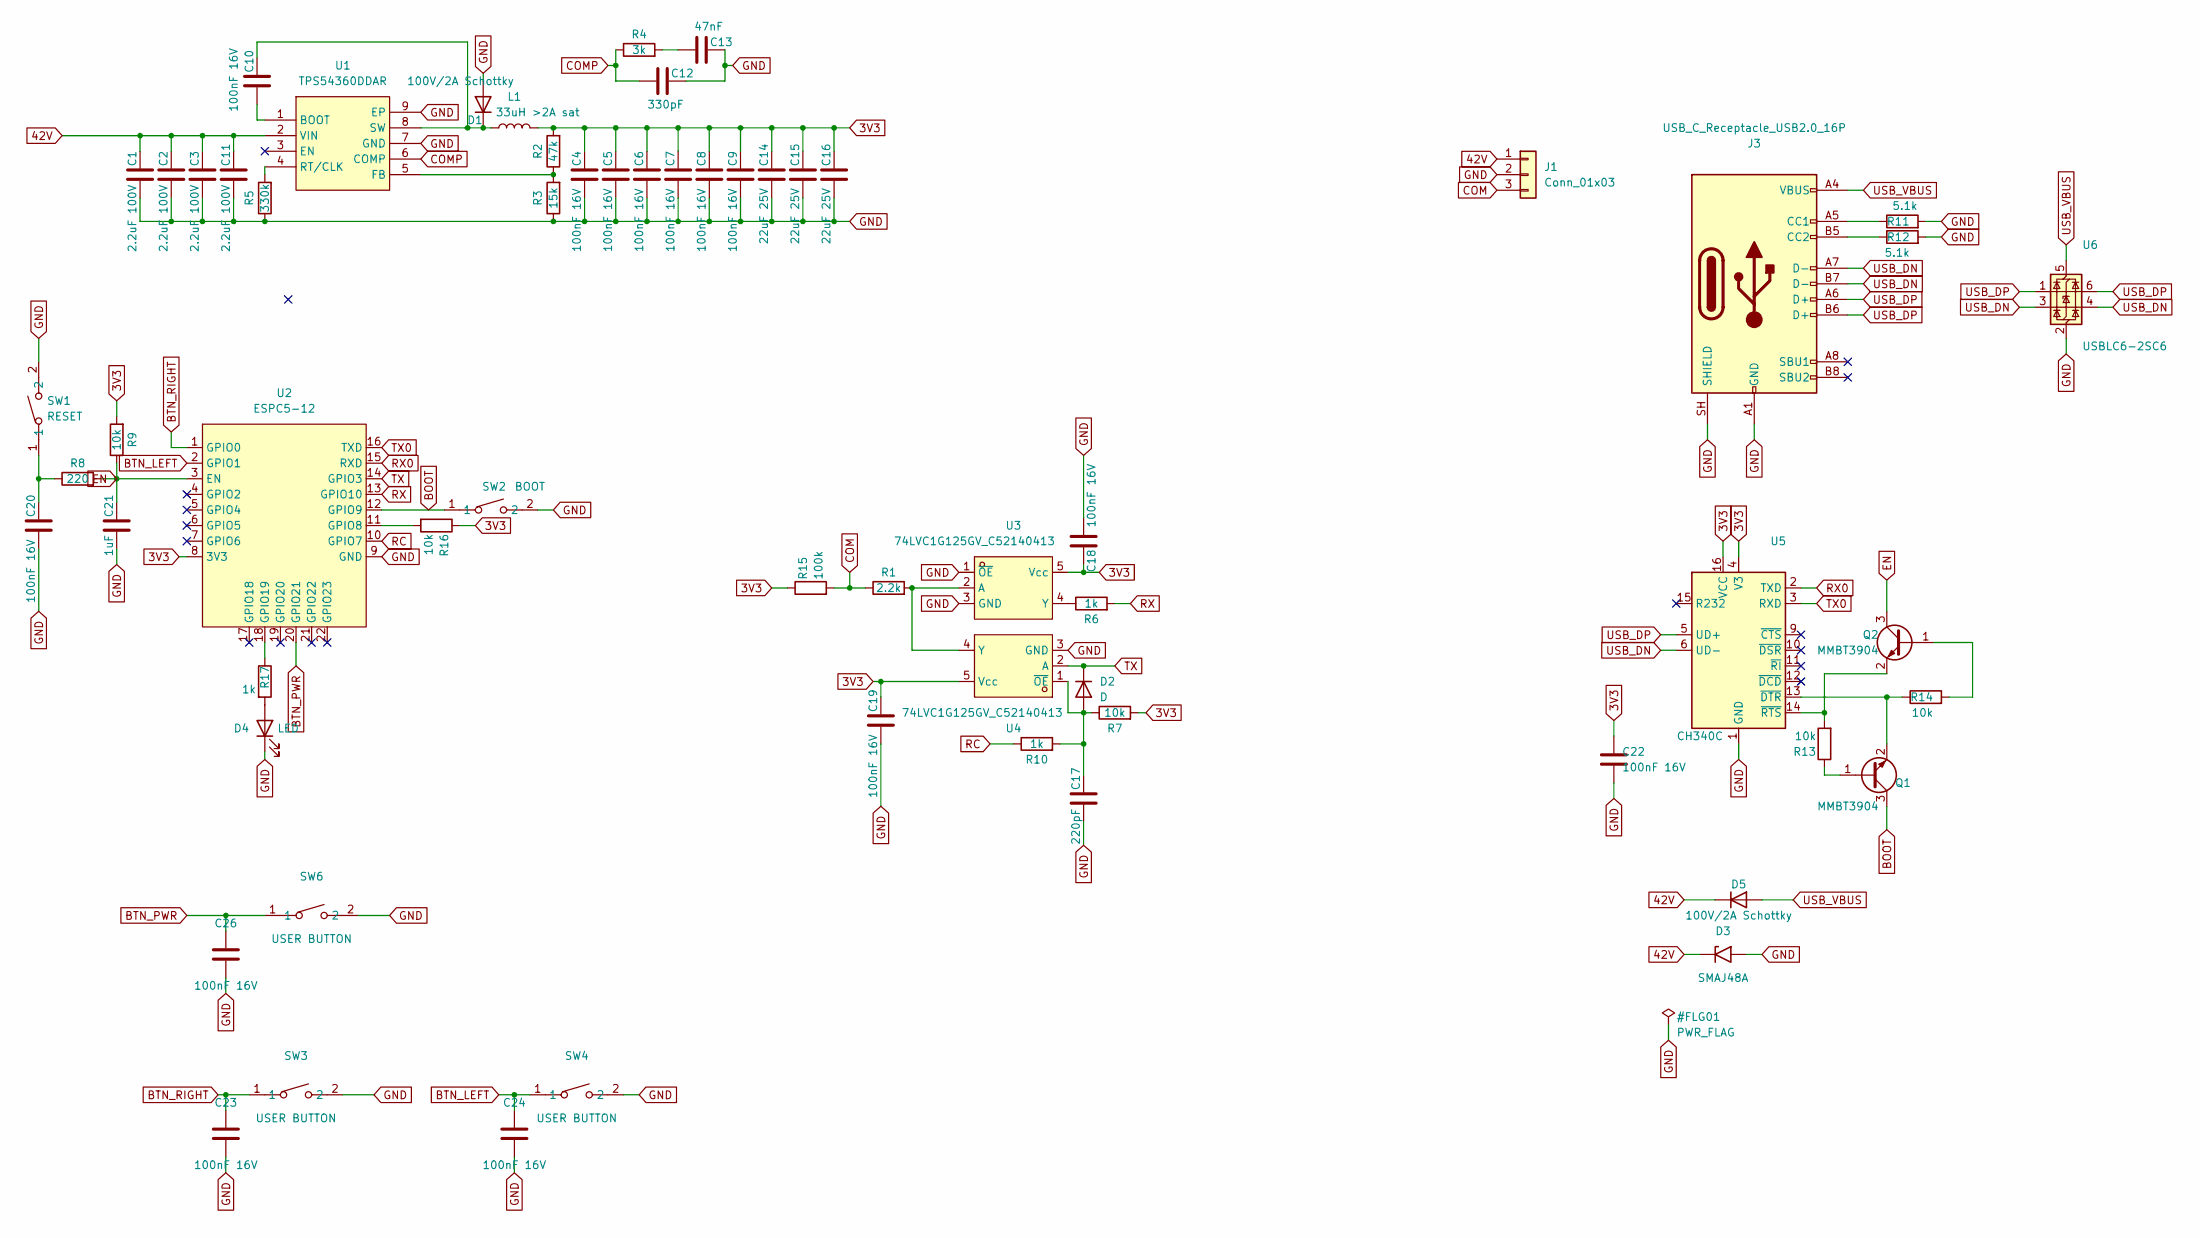
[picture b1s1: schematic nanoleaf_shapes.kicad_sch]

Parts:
C1, C2, C3, C11: 2.2uF 100V; C1210; LCSC C5449052
C4, C5, C6, C7, C8, C9, C10, C18, C19, C20, C22, C23, C24, C26: 100nF 16V; C0402; LCSC C1525
C12: 330pF; C0603; LCSC C1664
C13: 47nF; C0603; LCSC C1622
C14, C15, C16: 22uF 25V; C0805; LCSC C45783
C17: 220pF; C0402; LCSC C1530
C21: 1uF; C0402; LCSC C52923
D1: 100V/2A Schottky; SMA_L4.3-W2.6-LS5.2-RD; LCSC C14996
D2: D; D_SOD-123; LCSC C81598
D3: SMAJ48A; D_SMA; LCSC C41376401
D4: LED; LED_0603_1608Metric; LCSC C2290
D5: 100V/2A Schottky; D_SMA; LCSC C14996
J1: Conn_01x03; Nanoleaf_Linker_Pads
J3: USB_C_Receptacle_USB2.0_16P; USB_C_Receptacle_HRO_TYPE-C-31-M-12; LCSC C165948
L1: 33uH >2A sat; IND-SMD_L5.2-W5.2_YSPI0530; LCSC C20417191
Q1, Q2: MMBT3904; SOT-23; LCSC C7420353
R1: 2.2k; R0402; LCSC C25879
R2: 47k; R0402; LCSC C25792
R3: 15k; R0402; LCSC C25756
R4: 3k; R0603; LCSC C4211
R5: 330k; R0603; LCSC C23137
R6, R10, R17: 1k; R0402; LCSC C11702
R7, R9, R13, R14, R16: 10k; R0402; LCSC C25744
R8: 220; R0402; LCSC C25091
R11, R12: 5.1k; R0402; LCSC C25905
R15: 100k; R0402; LCSC C25741
SW1: RESET; SW_SPST_TS-1088-xR020; MPN TS-1088-AR02016; LCSC Part C720477
SW2: BOOT; SW_SPST_TS-1088-xR020; MPN TS-1088-AR02016; LCSC Part C720477
SW3, SW4, SW6: USER BUTTON; SW_Push_1P1T_XKB_TS-1187A; LCSC C318884
U1: TPS54360DDAR; SOIC-8_L5.0-W4.0-P1.27-LS6.0-BL-EP2.0; MPN TPS54360DDAR; LCSC Part C44377
U2: ESPC5-12; WT0132C6-S5; MPN ESPC5-12; LCSC Part C52139916
U3, U4: 74LVC1G125GV_C52140413; SOT-23-5_L3.0-W1.7-P0.95-LS2.8-BR; MPN 74LVC1G125GV; LCSC Part C52140413
U5: CH340C; SOIC-16_3.9x9.9mm_P1.27mm; LCSC C84681
U6: USBLC6-2SC6; SOT-23-6; LCSC C2827654

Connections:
3V3: C4.1, C5.1, C6.1, C7.1, C8.1, C9.1, C14.1, C15.1, C16.1, C18.1, C19.1, C22.1, L1.2, R2.2, R7.2, R9.2, R15.1, R16.1, U2.8 (3V3), U3.5 (Vcc), U4.5 (Vcc), U5.4 (V3), U5.16 (VCC)
42V: C1.1, C2.1, C3.1, C11.1, D3.1 (A1), D5.1 (K), J1.1, U1.2 (VIN)
BOOT: Q1.3 (C), SW2.1, U2.12 (GPIO9)
BTN_LEFT: C24.1, SW4.1, U2.2 (GPIO1)
BTN_PWR: C26.1, SW6.1, U2.20 (GPIO21)
BTN_RIGHT: C23.1, SW3.1, U2.1 (GPIO0)
COM: J1.3, R1.1, R15.2
COMP: C12.2, R4.1, U1.6 (COMP)
DTR: Q1.2 (E), R14.1, U5.13 (~DTR)
DTR_B: Q1.1 (B), R13.1
EN: C21.1, Q2.3 (C), R8.2, R9.1, U2.3 (EN)
GND: C1.2, C2.2, C3.2, C4.2, C5.2, C6.2, C7.2, C8.2, C9.2, C11.2, C12.1, C13.1, C14.2, C15.2, C16.2, C17.2, C18.2, C19.2, C20.2, C21.2, C22.2, C23.2, C24.2, C26.2, D1.2 (A), D3.2 (A2), D4.1 (K), J1.2, J3.A1 (GND), J3.A12 (GND), J3.B1 (GND), J3.B12 (GND), J3.SH (SHIELD), R3.1, R5.1, R11.2, R12.2, SW1.2, SW2.2, SW3.2, SW4.2, SW6.2, U1.7 (GND), U1.9 (EP), U2.9 (GND), U3.1 (~OE), U3.3 (GND), U4.3 (GND), U5.1 (GND), U6.2 (GND)
LED: R17.1, U2.18 (GPIO19)
LED_A: D4.2 (A), R17.2
unnamed: C13.2, R4.2
unnamed: C20.1, R8.1, SW1.1
unnamed: C10.1, D1.1 (K), L1.1, U1.8 (SW)
unnamed: C17.1, D2.2 (A), R7.1, R10.2, U4.1 (~OE)
unnamed: C10.2, U1.1 (BOOT)
unnamed: R2.1, R3.2, U1.5 (FB)
unnamed: R5.2, U1.4 (RT/CLK)
unnamed: R1.2, U3.2 (A), U4.4 (Y)
unnamed: R6.1, U3.4 (Y)
PAD11: R16.2, U2.11 (GPIO8)
RC: R10.1, U2.10 (GPIO7)
RTS: Q2.2 (E), R13.2, U5.14 (~RTS)
RTS_B: Q2.1 (B), R14.2
RX: R6.2, U2.13 (GPIO10)
RX0: U2.15 (RXD), U5.2 (TXD)
TX: D2.1 (K), U2.14 (GPIO3), U4.2 (A)
TX0: U2.16 (TXD), U5.3 (RXD)
USB_CC1: J3.A5 (CC1), R11.1
USB_CC2: J3.B5 (CC2), R12.1
USB_DN: J3.A7 (D-), J3.B7 (D-), U5.6 (UD-), U6.3 (I/O2), U6.4 (I/O2)
USB_DP: J3.A6 (D+), J3.B6 (D+), U5.5 (UD+), U6.1 (I/O1), U6.6 (I/O1)
USB_VBUS: D5.2 (A), J3.A4 (VBUS), J3.A9 (VBUS), J3.B4 (VBUS), J3.B9 (VBUS), U6.5 (VBUS)

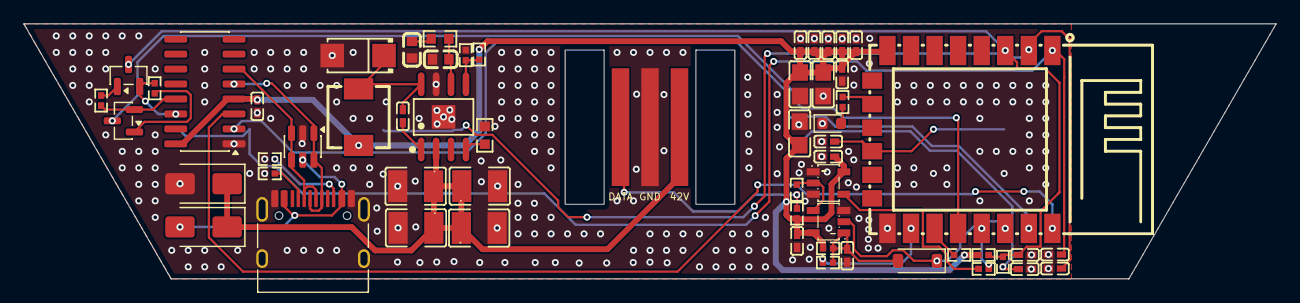
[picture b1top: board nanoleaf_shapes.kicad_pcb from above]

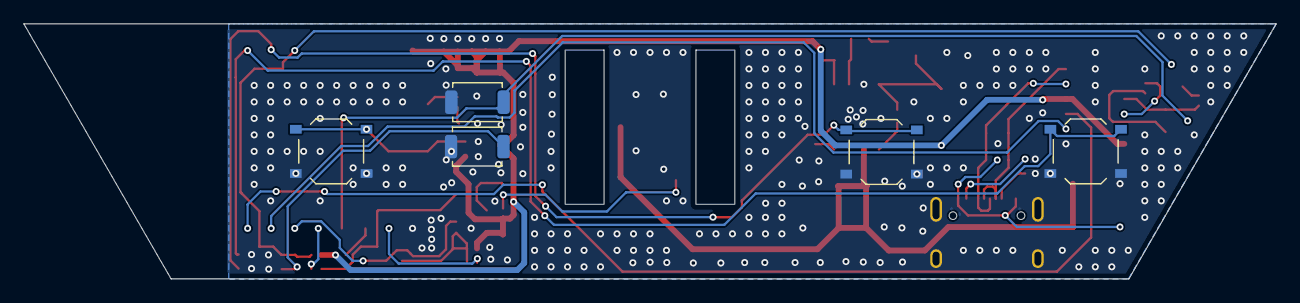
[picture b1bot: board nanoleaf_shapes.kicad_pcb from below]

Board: 2 copper layers, 106.3 x 21.7 mm, 63 parts (5 on the bottom side), 36 nets.
